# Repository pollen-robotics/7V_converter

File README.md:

# 7V_converter
This repository contains the KiCad project of the board used to convert the 12V power of the Reachy robot to 7.5V to power the motors of the head.

## Additional Components

This PCB can't work alone, it needs a few Components soldered on it:
- D24V25F7 converter
- 1x 22-03-5035 connectors at the top to connect a DXL module
- 2x 532530370 connectors at the bottom to connect 2x XL-320 motors

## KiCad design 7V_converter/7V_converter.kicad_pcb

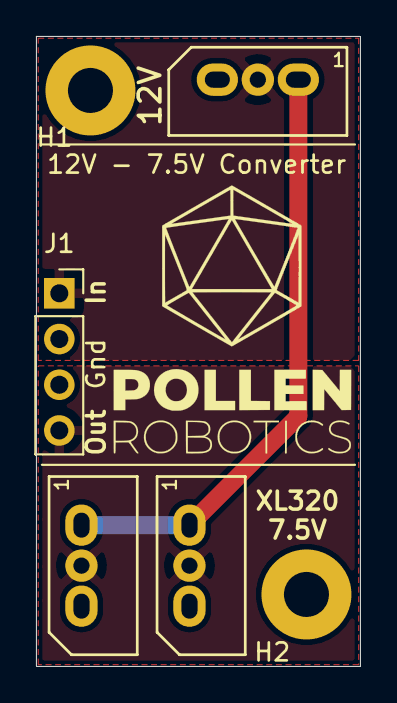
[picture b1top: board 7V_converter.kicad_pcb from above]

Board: 2 copper layers, 18.0 x 35.0 mm, 6 parts (0 on the bottom side), 4 nets.

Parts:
H1, H2: MountingHole; MountingHole_2.5mm_Pad
J1: Converter; PinSocket_1x04_P2.54mm_Vertical
J2: DXL_In; XL320_MX
J3: DXL_Out1; XL320_MX
J4: DXL_Out2; XL320_MX

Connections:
/DX_Data: J2.1, J3.1, J4.1
GND: J1.2, J1.3, J2.3, J3.3, J4.3
unnamed: J1.1, J2.2
unnamed: J1.4, J3.2, J4.2

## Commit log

2021-06-08 Initial commit.
